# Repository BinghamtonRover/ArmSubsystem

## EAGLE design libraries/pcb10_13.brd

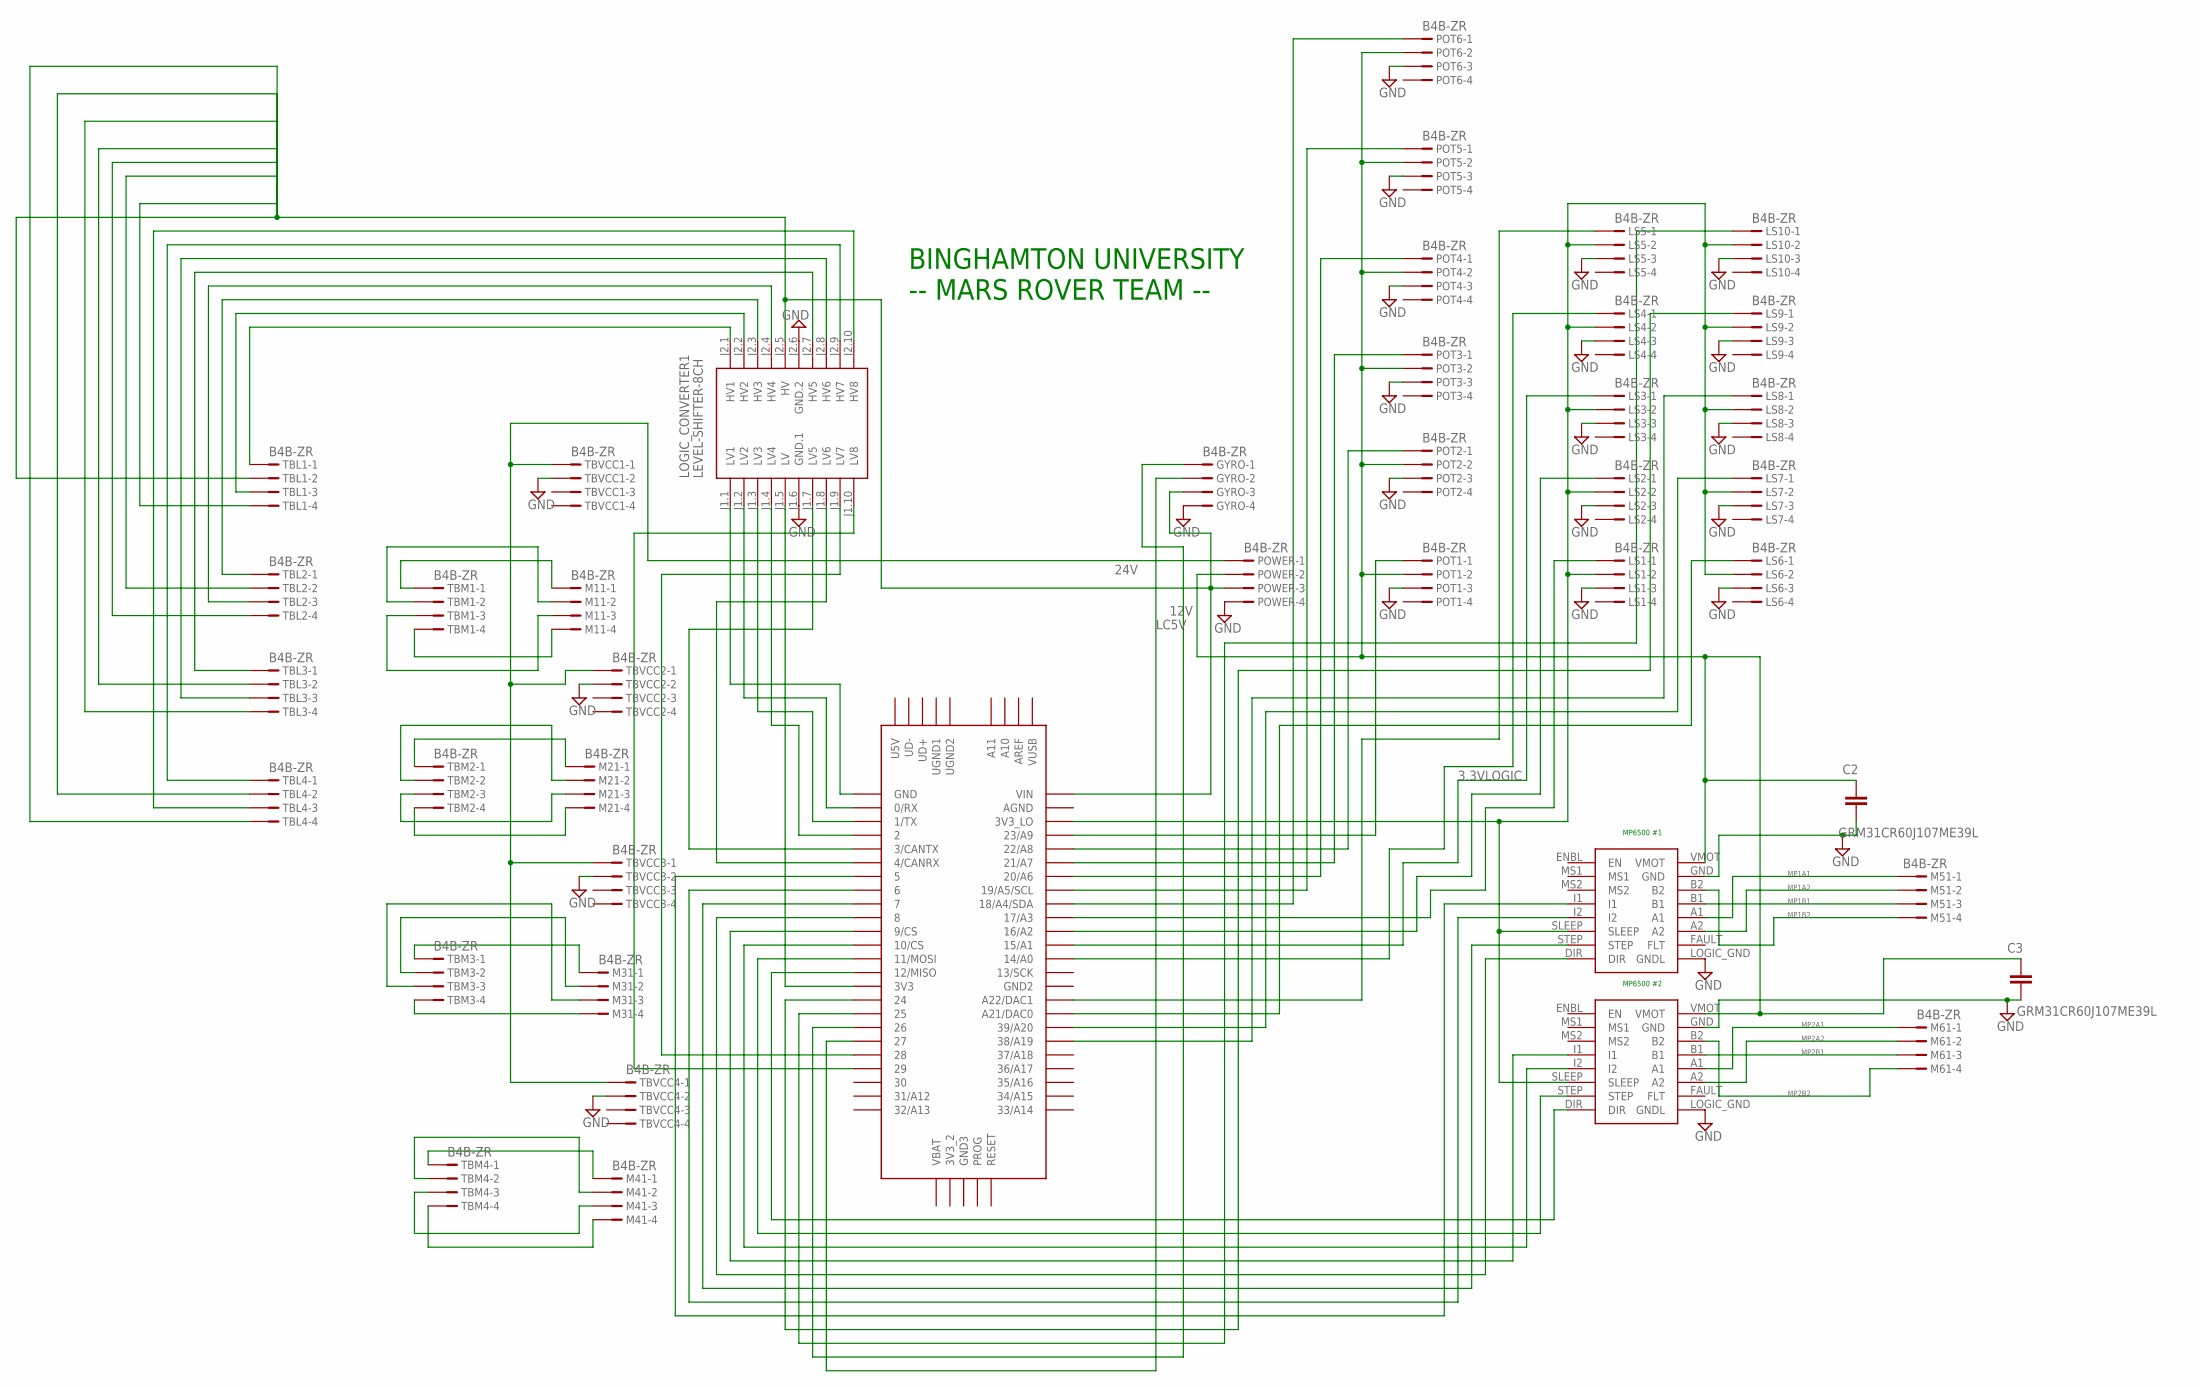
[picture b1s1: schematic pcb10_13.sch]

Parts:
C2, C3: GRM31CR60J107ME39L; CAP_1206
GYRO: B4B-ZR
LOGIC_CONVERTER1: LEVEL-SHIFTER-8CH
LS1, LS2, LS3, LS4, LS5, LS6, LS7, LS8, LS9, LS10: B4B-ZR
M11, M21, M31, M41, M51, M61: B4B-ZR
MP6500_3, MP6500_4: MP6500THROUGH_HOLE; MP6500
POT1, POT2, POT3, POT4, POT5, POT6: B4B-ZR
POWER: B4B-ZR
TBL1, TBL2, TBL3, TBL4: B4B-ZR
TBM1, TBM2, TBM3, TBM4: B4B-ZR
TBVCC1, TBVCC2, TBVCC3, TBVCC4: B4B-ZR
TEENSY4.2: TEENSY_3.5/3.6

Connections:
3.3VLOGIC: LS1.2, LS2.2, LS3.2, LS4.2, LS5.2, LS6.2, LS7.2, LS8.2, LS9.2, LS10.2, MP6500_3.SLEEP, MP6500_4.SLEEP, TEENSY4.2.3V3_LO
12V: C2.1, C3.1, MP6500_3.VMOT, MP6500_4.VMOT, POT1.2, POT2.2, POT3.2, POT4.2, POT5.2, POT6.2, POWER.2
24V: POWER.1, TBVCC1.1, TBVCC2.1, TBVCC3.1, TBVCC4.1
GND: C2.2, C3.2, GYRO.4, LOGIC_CONVERTER1.J1.6 (GND.1), LOGIC_CONVERTER1.J2.6 (GND.2), LS1.3, LS2.3, LS3.3, LS4.3, LS5.3, LS6.3, LS7.3, LS8.3, LS9.3, LS10.3, MP6500_3.GND, MP6500_3.LOGIC_GND (GNDL), MP6500_4.GND, MP6500_4.LOGIC_GND (GNDL), POT1.3, POT2.3, POT3.3, POT4.3, POT5.3, POT6.3, POWER.4, TBVCC1.2, TBVCC2.2, TBVCC3.2, TBVCC4.2
GYRO1: GYRO.1, TEENSY4.2.26
GYRO2: GYRO.2, TEENSY4.2.27
LC1CH1: LOGIC_CONVERTER1.J2.1 (HV1), TBL1.1
LC1CH2: LOGIC_CONVERTER1.J2.2 (HV2), TBL1.3
LC1CH3: LOGIC_CONVERTER1.J2.3 (HV3), TBL2.1
LC1CH4: LOGIC_CONVERTER1.J2.4 (HV4), TBL2.3
LC1CH5: LOGIC_CONVERTER1.J2.7 (HV5), TBL3.1
LC1CH6: LOGIC_CONVERTER1.J2.8 (HV6), TBL3.3
LC1CH7: LOGIC_CONVERTER1.J2.9 (HV7), TBL4.1
LC1CH8: LOGIC_CONVERTER1.J2.10 (HV8), TBL4.3
LC2CH1: LOGIC_CONVERTER1.J1.1 (LV1), TEENSY4.2.GND
LC2CH2: LOGIC_CONVERTER1.J1.2 (LV2), TEENSY4.2.0/RX
LC2CH3: LOGIC_CONVERTER1.J1.3 (LV3), TEENSY4.2.1/TX
LC2CH4: LOGIC_CONVERTER1.J1.4 (LV4), TEENSY4.2.2
LC2CH5: LOGIC_CONVERTER1.J1.7 (LV5), TEENSY4.2.3/CANTX
LC2CH6: LOGIC_CONVERTER1.J1.8 (LV6), TEENSY4.2.4/CANRX
LC2CH7: LOGIC_CONVERTER1.J1.9 (LV7), TEENSY4.2.28
LC2CH8: LOGIC_CONVERTER1.J1.10 (LV8), TEENSY4.2.29
LC3.3V: LOGIC_CONVERTER1.J1.5 (LV), TEENSY4.2.3V3
LC5V: GYRO.3, LOGIC_CONVERTER1.J2.5 (HV), POWER.3, TBL1.2, TBL1.4, TBL2.2, TBL2.4, TBL3.2, TBL3.4, TBL4.2, TBL4.4, TEENSY4.2.VIN
LS1-1OUT: LS1.1, TEENSY4.2.17/A3
LS2-1OUT: LS2.1, TEENSY4.2.16/A2
LS3-1OUT: LS3.1, TEENSY4.2.15/A1
LS4-1OUT: LS4.1, TEENSY4.2.14/A0
LS5-1OUT: LS5.1, TEENSY4.2.A22/DAC1
LS6-1OUT: LS6.1, TEENSY4.2.21/DAC0 (A21/DAC0)
LS7-1OUT: LS7.1, TEENSY4.2.39/A20
LS8-1OUT: LS8.1, TEENSY4.2.38/A19
LS9-1OUT: LS9.1, TEENSY4.2.24
LS10-1OUT: LS10.1, TEENSY4.2.25
MP1-I1: MP6500_3.I1, TEENSY4.2.5
MP1-I2: MP6500_3.I2, TEENSY4.2.6
MP1A1: M51.1, MP6500_3.A1
MP1A2: M51.2, MP6500_3.A2
MP1B1: M51.3, MP6500_3.B1
MP1B2: M51.4, MP6500_3.B2
MP1DIR: MP6500_3.DIR, TEENSY4.2.8
MP1STEP: MP6500_3.STEP, TEENSY4.2.7
MP2-I1: MP6500_4.I1, TEENSY4.2.9/CS
MP2-I2: MP6500_4.I2, TEENSY4.2.10/CS
MP2A1: M61.1, MP6500_4.A1
MP2A2: M61.2, MP6500_4.A2
MP2B1: M61.3, MP6500_4.B1
MP2B2: M61.4, MP6500_4.B2
MP2DIR: MP6500_4.DIR, TEENSY4.2.12/MISO
MP2STEP: MP6500_4.STEP, TEENSY4.2.11/MOSI
POT1-1OUT: POT1.1, TEENSY4.2.23/A9
POT2-1OUT: POT2.1, TEENSY4.2.22/A8
POT3-1OUT: POT3.1, TEENSY4.2.21/A7
POT4-1OUT: POT4.1, TEENSY4.2.20/A6
POT5-1OUT: POT5.1, TEENSY4.2.19/A5/SCL
POT6-1OUT: POT6.1, TEENSY4.2.18/A4/SDA
TBM1-1OUT: M11.1, TBM1.1
TBM1-2OUT: M11.2, TBM1.2
TBM1-3OUT: M11.3, TBM1.3
TBM1-4OUT: M11.4, TBM1.4
TBM2-1OUT: M21.1, TBM2.1
TBM2-2OUT: M21.2, TBM2.2
TBM2-3OUT: M21.3, TBM2.3
TBM2-4OUT: M21.4, TBM2.4
TBM3-1OUT: M31.1, TBM3.1
TBM3-2OUT: M31.2, TBM3.2
TBM3-3OUT: M31.3, TBM3.3
TBM3-4OUT: M31.4, TBM3.4
TBM4-1OUT: M41.1, TBM4.1
TBM4-2OUT: M41.2, TBM4.2
TBM4-3OUT: M41.3, TBM4.3
TBM4-4OUT: M41.4, TBM4.4

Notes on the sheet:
BINGHAMTON UNIVERSITY -- MARS ROVER TEAM --
MP6500 #1
MP6500 #2

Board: 2 copper layers, 42 parts (0 on the bottom side), 72 nets, no tracks yet.

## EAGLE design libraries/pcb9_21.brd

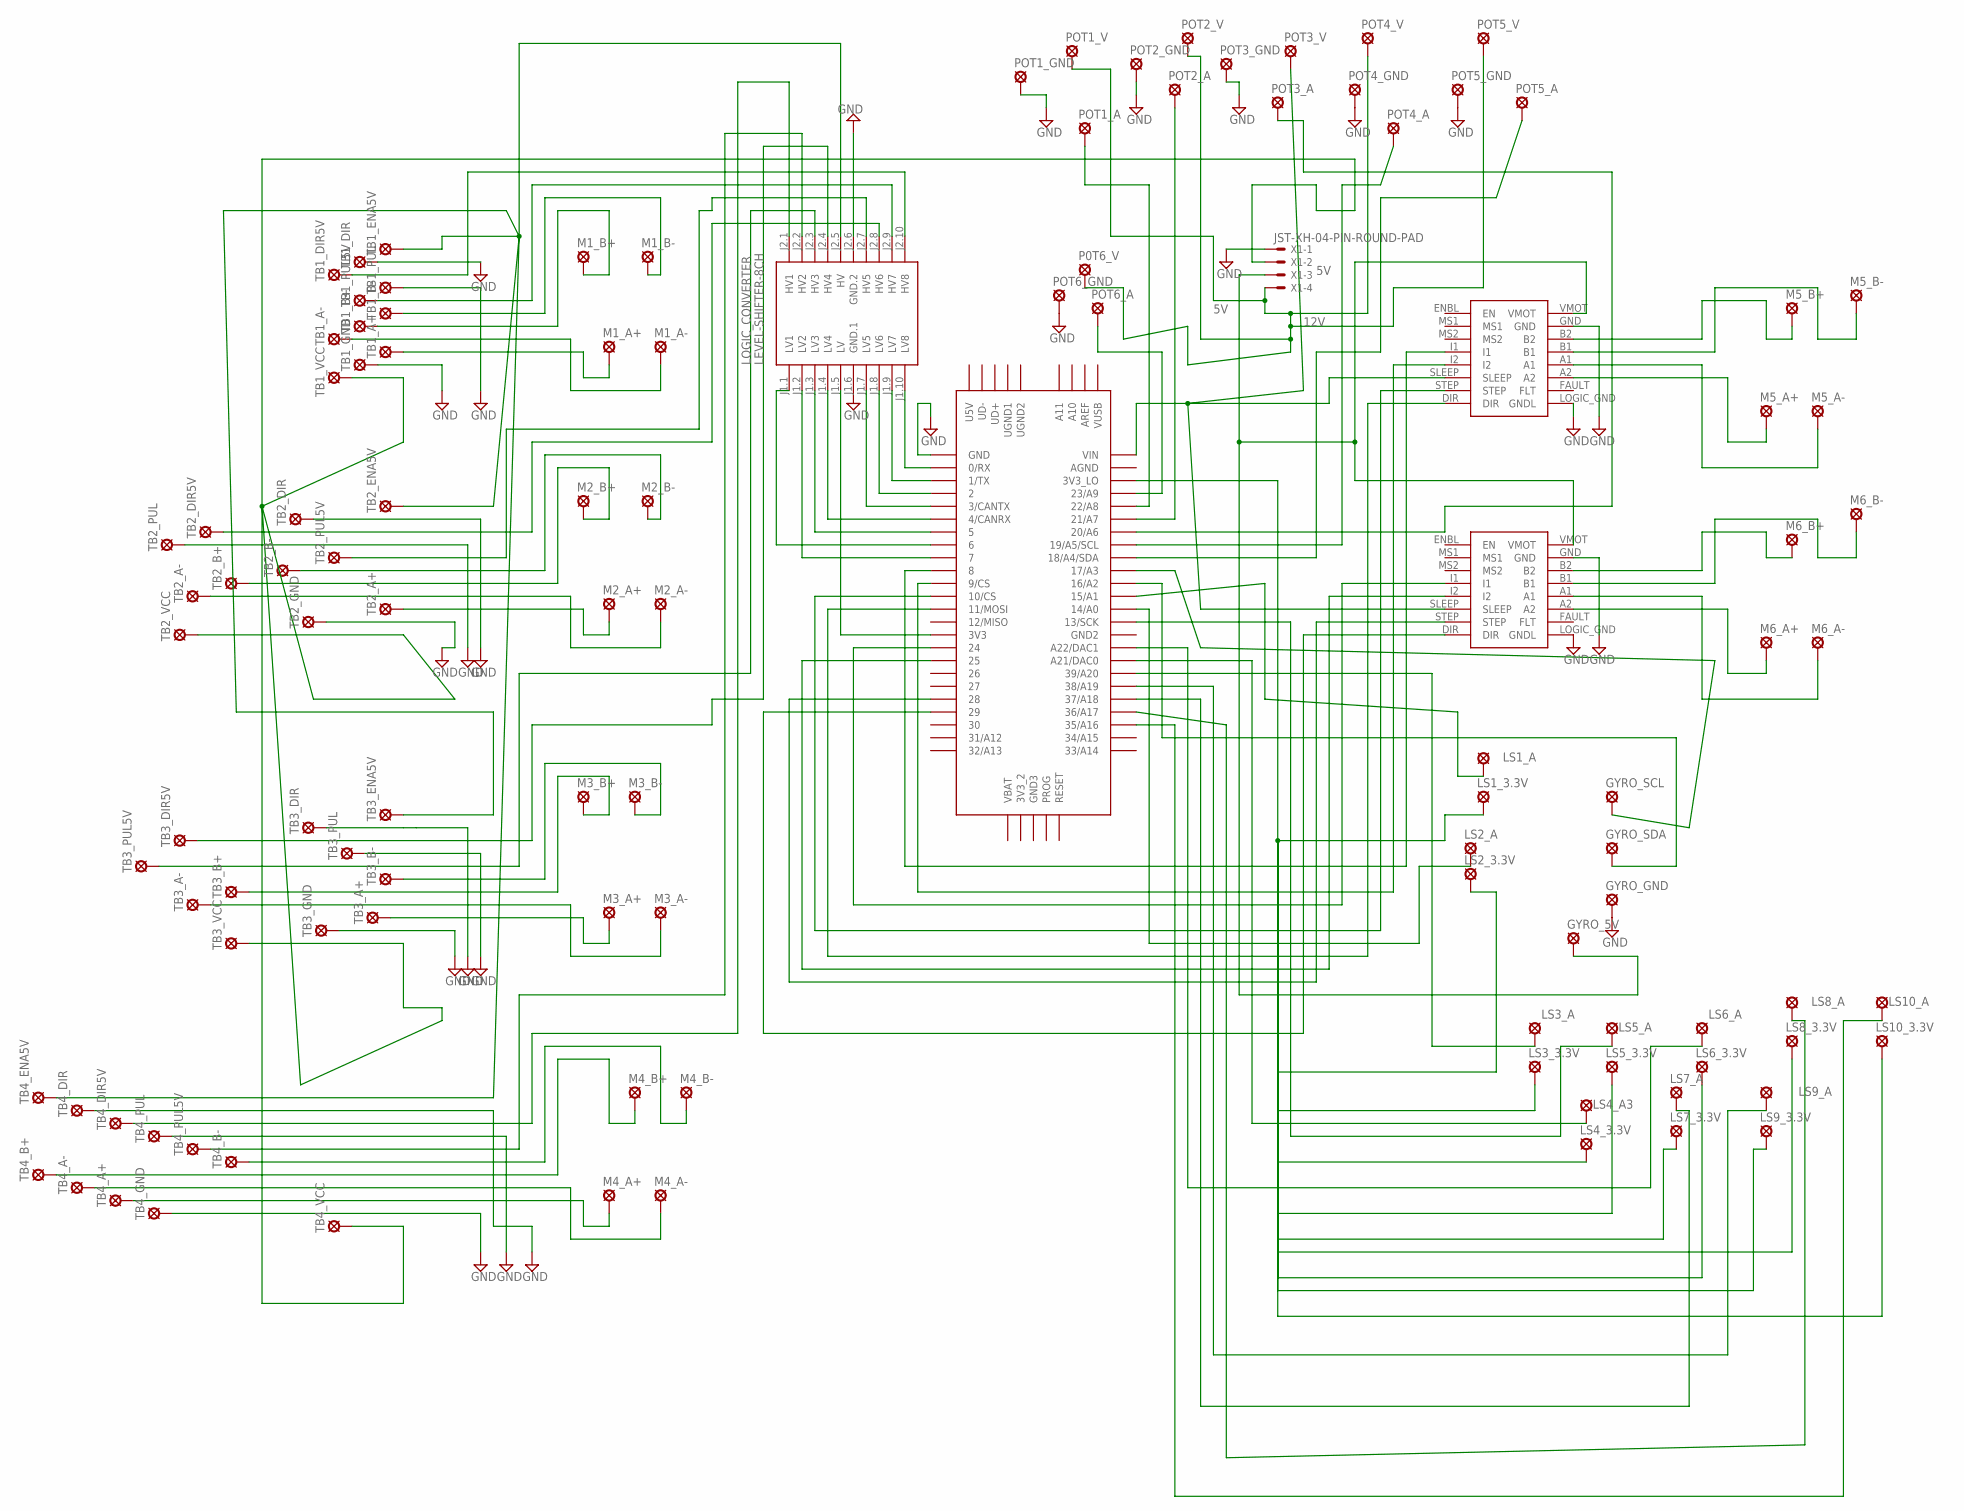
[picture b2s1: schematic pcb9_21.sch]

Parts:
GYRO_5V: LSP11
GYRO_GND: LSP11
GYRO_SCL: LSP11
GYRO_SDA: LSP11
LOGIC_CONVERTER: LEVEL-SHIFTER-8CH
LS1_3.3V, LS1_A, LS2_3.3V, LS2_A, LS3_3.3V, LS3_A, LS4_3.3V, LS4_A3, LS5_3.3V, LS5_A, LS6_3.3V, LS6_A, LS7_3.3V, LS7_A, LS8_3.3V, LS8_A, LS9_3.3V, LS9_A, LS10_3.3V, LS10_A: LSP11
M1_A+, M1_A-, M1_B+, M1_B-, M2_A+, M2_A-, M2_B+, M2_B-, M3_A+, M3_A-, M3_B+, M3_B-, M4_A+, M4_A-, M4_B+, M4_B-, M5_A+, M5_A-, M5_B+, M5_B-, M6_A+, M6_A-, M6_B+, M6_B-: LSP11
MP6500_1, MP6500_2: MP6500THROUGH_HOLE; MP6500
P0T6_V: LSP11
POT1_A, POT1_GND, POT1_V, POT2_A, POT2_GND, POT2_V, POT3_A, POT3_GND, POT3_V, POT4_A, POT4_GND, POT4_V, POT5_A, POT5_GND, POT5_V, POT6_A, POT6_GND: LSP11
TB1_A+, TB1_A-, TB1_B+, TB1_B-, TB1_DIR, TB1_DIR5V, TB1_ENA5V, TB1_GND, TB1_PUL, TB1_PUL5V, TB1_VCC, TB2_A+, TB2_A-, TB2_B+, TB2_B-, TB2_DIR, TB2_DIR5V, TB2_ENA5V, TB2_GND, TB2_PUL, TB2_PUL5V, TB2_VCC, TB3_A+, TB3_A-, TB3_B+, TB3_B-, TB3_DIR, TB3_DIR5V, TB3_ENA5V, TB3_GND, TB3_PUL, TB3_PUL5V, TB3_VCC, TB4_A+, TB4_A-, TB4_B+, TB4_B-, TB4_DIR, TB4_DIR5V, TB4_ENA5V, TB4_GND, TB4_PUL, TB4_PUL5V, TB4_VCC: LSP11
TEENSY4.1: TEENSY_3.5/3.6
X1: JST-XH-04-PIN-ROUND-PAD; JST-XH-04-PACKAGE-ROUND-PAD

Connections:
5V: GYRO_5V.MP, MP6500_1.VMOT, MP6500_2.VMOT, TB1_VCC.MP, TB2_VCC.MP, TB3_VCC.MP, TB4_VCC.MP, X1.2, X1.3
12V: P0T6_V.MP, POT1_V.MP, POT2_V.MP, POT4_V.MP, POT5_V.MP, X1.4
GND: GYRO_GND.MP, LOGIC_CONVERTER.J1.6 (GND.1), LOGIC_CONVERTER.J2.6 (GND.2), MP6500_1.GND, MP6500_1.LOGIC_GND (GNDL), MP6500_2.GND, MP6500_2.LOGIC_GND (GNDL), POT1_GND.MP, POT2_GND.MP, POT3_GND.MP, POT4_GND.MP, POT5_GND.MP, POT6_GND.MP, TB1_DIR.MP, TB1_GND.MP, TB1_PUL.MP, TB2_DIR.MP, TB2_GND.MP, TB2_PUL.MP, TB3_DIR.MP, TB3_GND.MP, TB3_PUL.MP, TB4_DIR.MP, TB4_GND.MP, TB4_PUL.MP, TEENSY4.1.GND, X1.1
unnamed: M1_A+.MP, TB1_A+.MP
unnamed: M1_A-.MP, TB1_A-.MP
unnamed: M1_B+.MP, TB1_B+.MP
unnamed: M1_B-.MP, TB1_B-.MP
unnamed: M2_A+.MP, TB2_A+.MP
unnamed: M2_A-.MP, TB2_A-.MP
unnamed: M2_B+.MP, TB2_B+.MP
unnamed: M2_B-.MP, TB2_B-.MP
unnamed: M3_A+.MP, TB3_A+.MP
unnamed: M3_A-.MP, TB3_A-.MP
unnamed: M3_B+.MP, TB3_B+.MP
unnamed: M3_B-.MP, TB3_B-.MP
unnamed: M4_A+.MP, TB4_A+.MP
unnamed: M4_A-.MP, TB4_A-.MP
unnamed: M4_B+.MP, TB4_B+.MP
unnamed: M4_B-.MP, TB4_B-.MP
unnamed: LOGIC_CONVERTER.J2.9 (HV7), TB1_PUL5V.MP
unnamed: LOGIC_CONVERTER.J2.8 (HV6), TB2_DIR5V.MP
unnamed: LOGIC_CONVERTER.J1.7 (LV5), TEENSY4.1.3/CANTX
unnamed: LOGIC_CONVERTER.J2.10 (HV8), TB1_DIR5V.MP
unnamed: LOGIC_CONVERTER.J2.4 (HV4), TB3_DIR5V.MP
unnamed: LOGIC_CONVERTER.J1.4 (LV4), TEENSY4.1.4/CANRX
unnamed: LOGIC_CONVERTER.J1.1 (LV1), TEENSY4.1.6
unnamed: LOGIC_CONVERTER.J1.2 (LV2), TEENSY4.1.7
unnamed: M5_A+.MP, MP6500_1.A2
unnamed: M5_A-.MP, MP6500_1.A1
unnamed: POT6_A.MP, TEENSY4.1.23/A9
unnamed: M5_B-.MP, MP6500_1.B1
unnamed: M5_B+.MP, MP6500_1.B2
unnamed: M6_A+.MP, MP6500_2.A2
unnamed: M6_A-.MP, MP6500_2.A1
unnamed: M6_B-.MP, MP6500_2.B1
unnamed: M6_B+.MP, MP6500_2.B2
unnamed: MP6500_1.I1, TEENSY4.1.8
unnamed: MP6500_1.I2, TEENSY4.1.9/CS
unnamed: MP6500_1.STEP, TEENSY4.1.10/CS
unnamed: MP6500_1.DIR, TEENSY4.1.11/MOSI
unnamed: MP6500_2.I1, TEENSY4.1.24
unnamed: MP6500_2.I2, TEENSY4.1.25
unnamed: MP6500_2.STEP, TEENSY4.1.28
unnamed: MP6500_2.DIR, TEENSY4.1.29
unnamed: POT1_A.MP, TEENSY4.1.22/A8
unnamed: LOGIC_CONVERTER.J1.9 (LV7), TEENSY4.1.1/TX
unnamed: LOGIC_CONVERTER.J1.10 (LV8), TEENSY4.1.0/RX
unnamed: LOGIC_CONVERTER.J1.8 (LV6), TEENSY4.1.2
unnamed: LOGIC_CONVERTER.J2.3 (HV3), TB3_PUL5V.MP
unnamed: LOGIC_CONVERTER.J2.7 (HV5), TB2_PUL5V.MP
unnamed: LOGIC_CONVERTER.J1.3 (LV3), TEENSY4.1.5
unnamed: LOGIC_CONVERTER.J2.2 (HV2), TB4_PUL5V.MP
unnamed: LS5_A.MP, TEENSY4.1.13/SCK
unnamed: LOGIC_CONVERTER.J1.5 (LV), TEENSY4.1.3V3
unnamed: LOGIC_CONVERTER.J2.1 (HV1), TB4_DIR5V.MP
unnamed: POT2_A.MP, TEENSY4.1.21/A7
unnamed: POT3_A.MP, TEENSY4.1.20/A6
unnamed: POT4_A.MP, TEENSY4.1.19/A5/SCL
unnamed: MP6500_1.SLEEP, MP6500_2.SLEEP, POT3_V.MP, TEENSY4.1.VIN
unnamed: GYRO_SCL.MP, TEENSY4.1.17/A3
unnamed: GYRO_SDA.MP, TEENSY4.1.16/A2
unnamed: LS1_A.MP, TEENSY4.1.15/A1
unnamed: LS1_3.3V.MP, LS2_3.3V.MP, LS3_3.3V.MP, LS4_3.3V.MP, LS5_3.3V.MP, LS6_3.3V.MP, LS7_3.3V.MP, LS8_3.3V.MP, LS9_3.3V.MP, LS10_3.3V.MP, TEENSY4.1.3V3_LO
unnamed: POT5_A.MP, TEENSY4.1.18/A4/SDA
unnamed: LOGIC_CONVERTER.J2.5 (HV), TB1_ENA5V.MP, TB2_ENA5V.MP, TB3_ENA5V.MP, TB4_ENA5V.MP
unnamed: LS2_A.MP, TEENSY4.1.14/A0
unnamed: LS3_A.MP, TEENSY4.1.39/A20
unnamed: LS6_A.MP, TEENSY4.1.A22/DAC1
unnamed: LS4_A3.MP, TEENSY4.1.21/DAC0 (A21/DAC0)
unnamed: LS9_A.MP, TEENSY4.1.38/A19
unnamed: LS7_A.MP, TEENSY4.1.37/A18
unnamed: LS8_A.MP, TEENSY4.1.36/A17
unnamed: LS10_A.MP, TEENSY4.1.35/A16

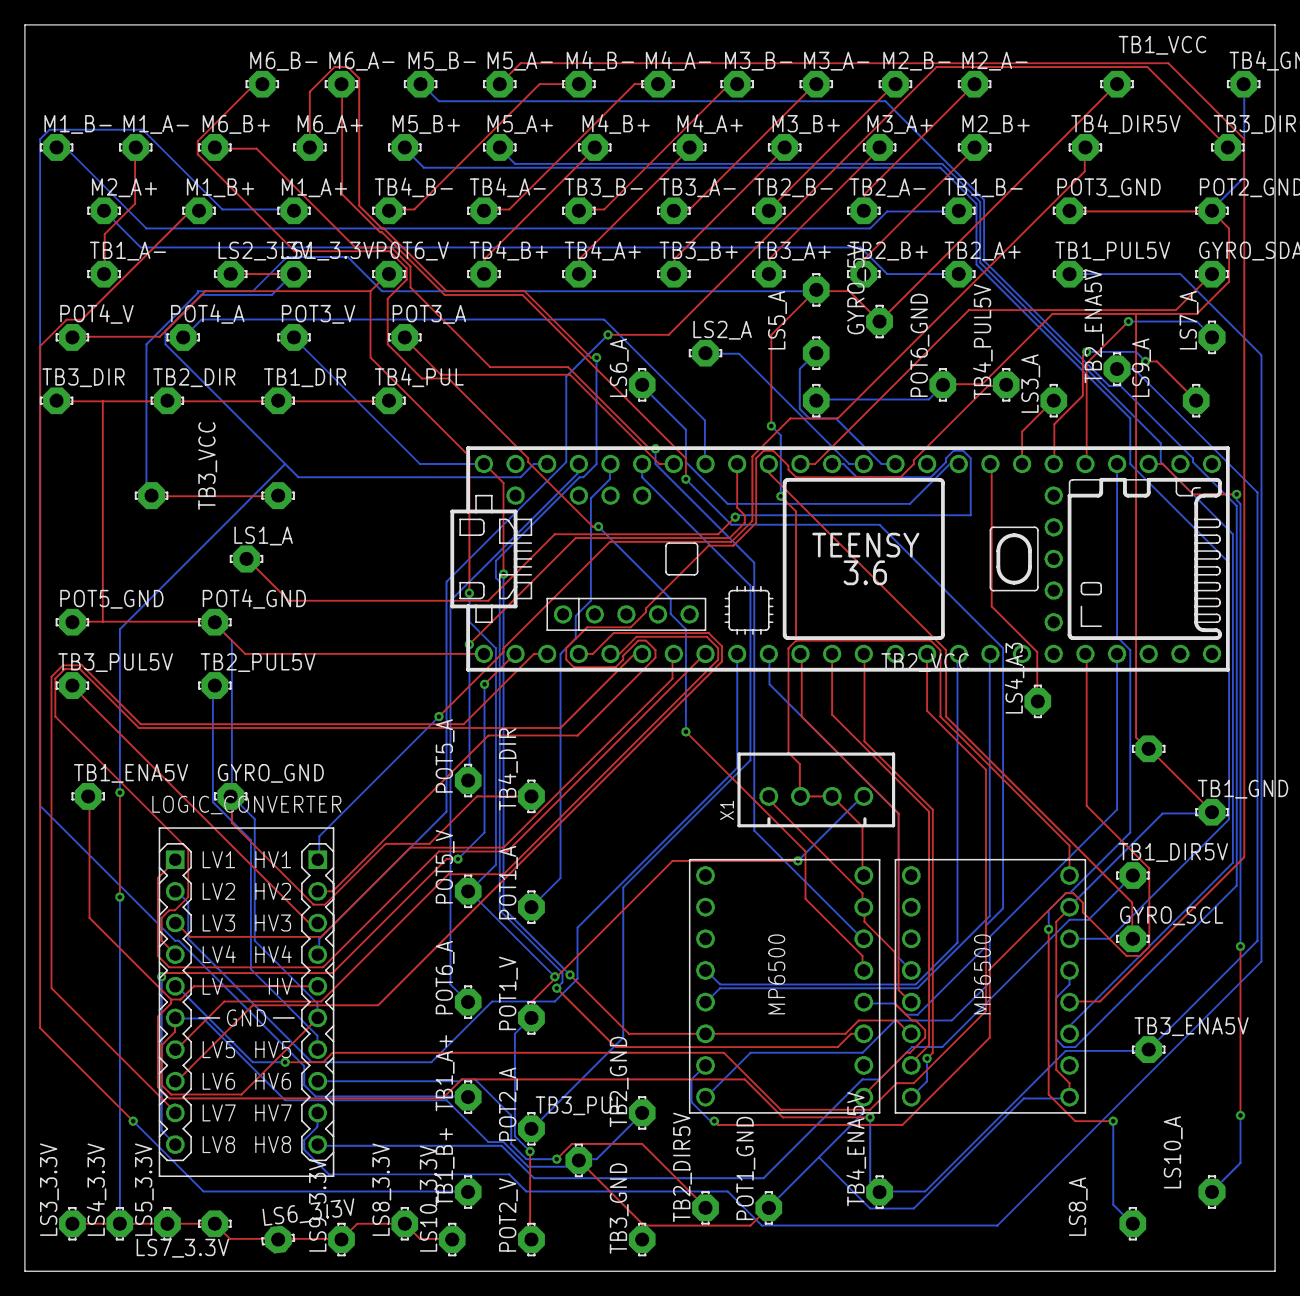
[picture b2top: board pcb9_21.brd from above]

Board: 2 copper layers, 100.3 x 100.0 mm, 115 parts (0 on the bottom side), 73 nets.

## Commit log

2020-10-08 Add files via upload
    - modified & labeled netlist
    - jst footprints completed
    - capacitor added for mp6500 in design
    - limit switches added and hooked up to correct voltages
    - drivers are connected to appropriate logic and voltage grades
2020-10-08 Updated PCB (10/5)

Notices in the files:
parts and their libraries:
diy-modules: Released under the Creative Commons Attribution 4.0 International License: http://creativecommons.org/licenses/by/4.0
